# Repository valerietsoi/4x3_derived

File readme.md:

# 4x3 derived

## description 
4x3, four columns and three rows.

Derived, as in derived from the [previous 2x2 macropad](https://github.com/valerietsoi/2squared).

PCB and firmware tested.

Stabless only.

<br>

## pics
| | |
| --- | --- |
|  | |
|  |  |
|  |  |
<br>

## firmware

Use [QMK toolbox](https://qmk.fm/toolbox) to flash the pre-compiled `.bin`. Source files to be uploaded.

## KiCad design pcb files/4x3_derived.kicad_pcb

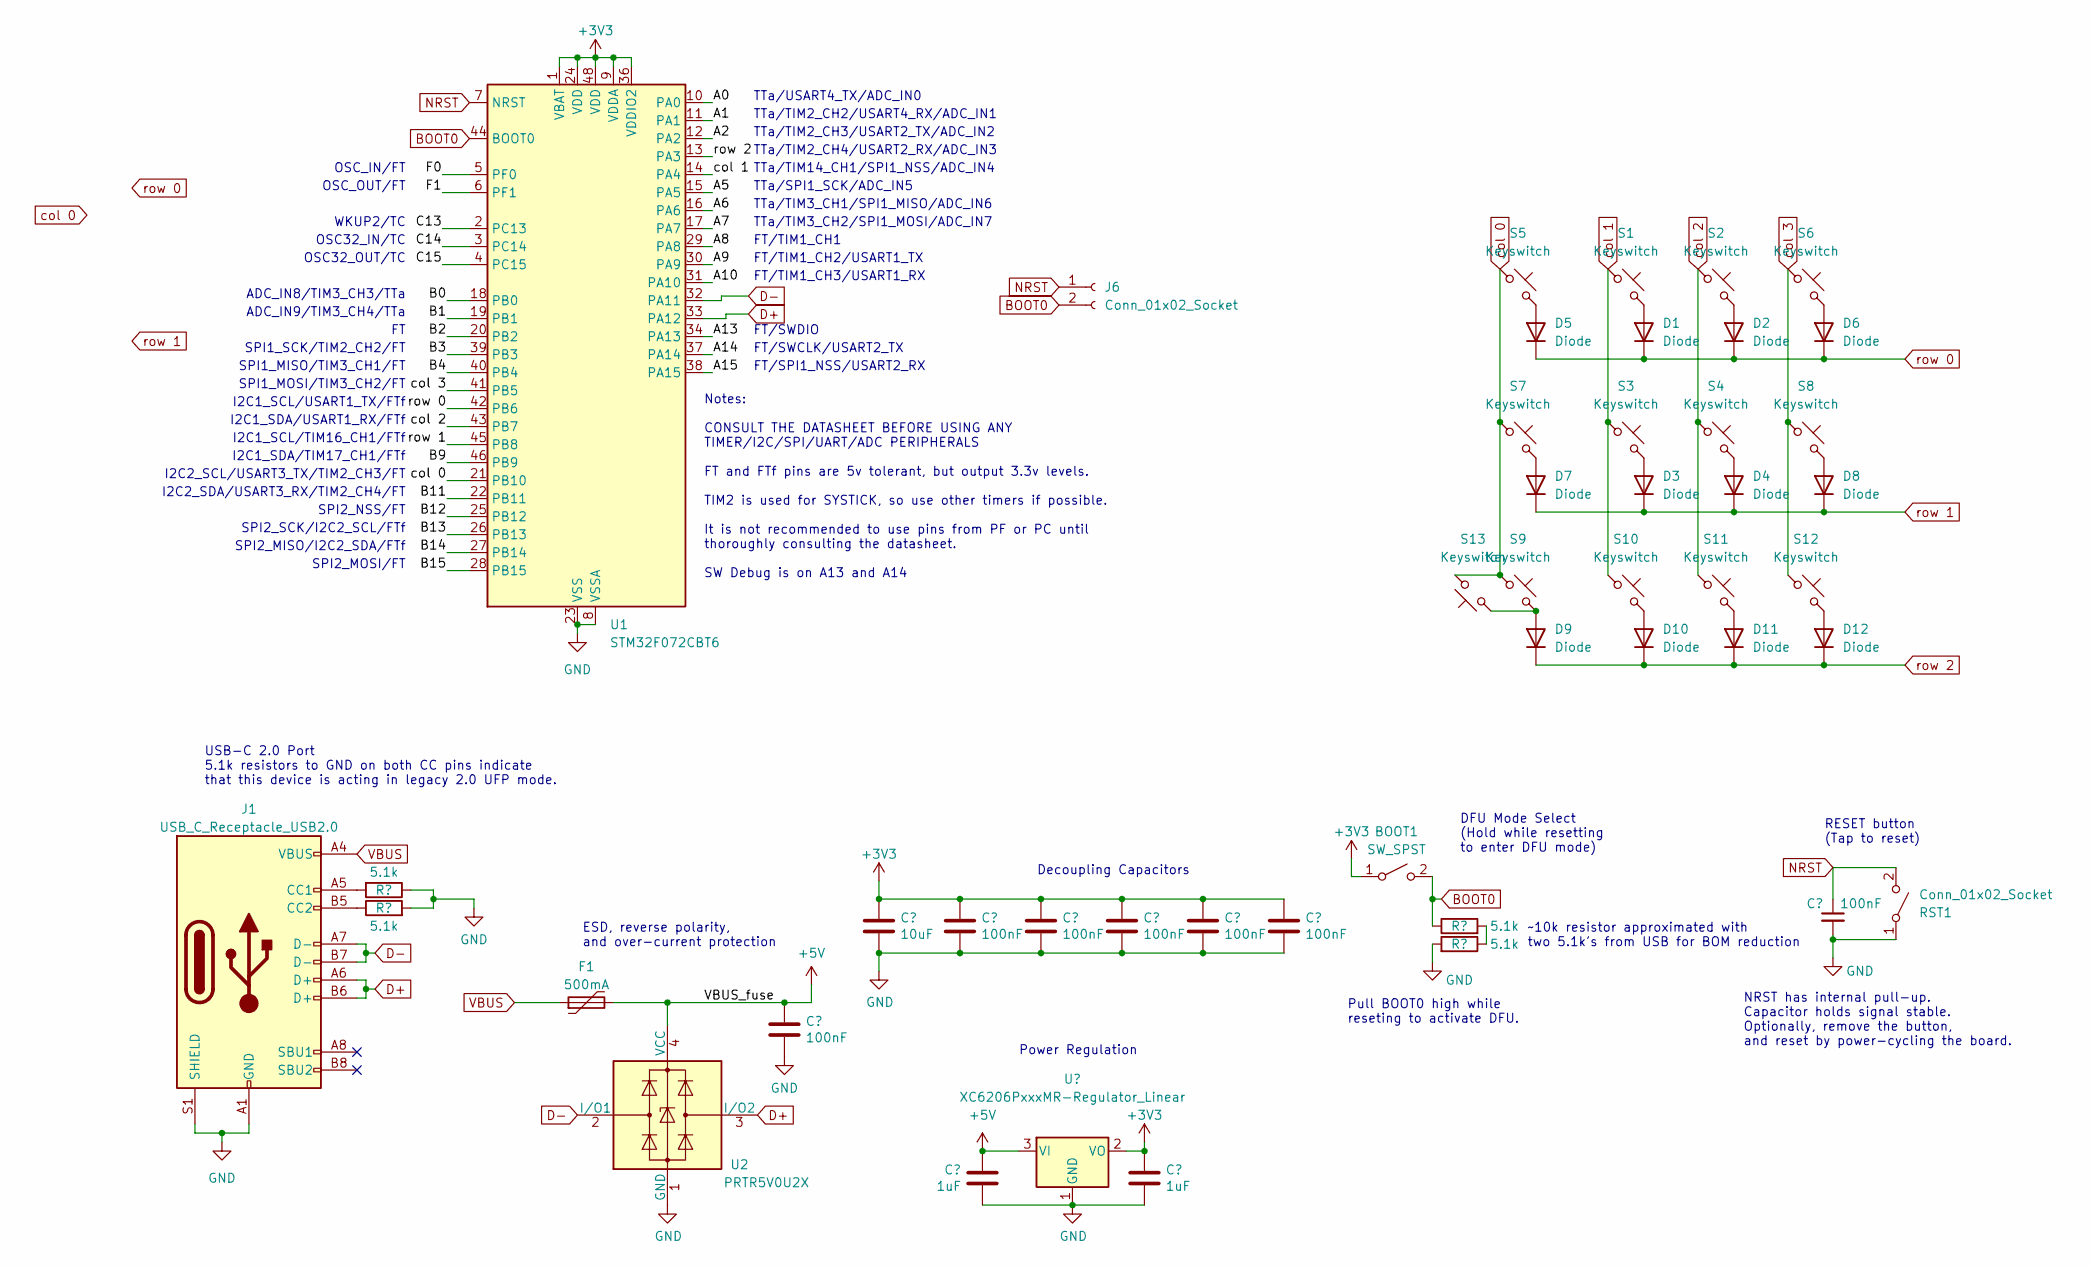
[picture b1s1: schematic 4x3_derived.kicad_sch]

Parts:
BOOT1: SW_SPST; SW_SPST_TL3342
C1, C3, C4, C5, C6, C7, C8: 100nF; C_0402_1005Metric; LCSC C307331
C2: 10uF; C_0603_1608Metric; LCSC C307331
C9, C10: 1uF; C_0402_1005Metric; LCSC C307331
D1, D2, D3, D4, D5, D6, D7, D8, D9, D10, D11, D12: Diode; Diode_SOD-123
F1: 500mA; Fuse_1206_3216Metric; LCSC C135341
J1: USB_C_Receptacle_USB2.0; USB_C_Receptacle_HRO_TYPE-C-31-M-12; JlcRotOffset 180
J6: Conn_01x02_Socket; PinHeader_1x02_P2.54mm_Vertical
R1, R2, R3, R4: 5.1k; R_0402_1005Metric
RST1: Conn_01x02_Socket; PinHeader_1x02_P2.54mm_Vertical
S1, S2, S3, S4, S5, S6, S7, S8, S9, S10, S11, S12, S13: Keyswitch; Hotswap_MX_Plated_1.00u
U1: STM32F072CBT6; LQFP-48_7x7mm_P0.5mm; JlcRotOffset 90
U2: PRTR5V0U2X; SOT-143; LCSC C2827688
U3: XC6206PxxxMR-Regulator_Linear; SOT-23; LCSC C5446

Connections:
/A0: U1.10 (PA0)
/A1: U1.11 (PA1)
/A2: U1.12 (PA2)
/A5: U1.15 (PA5)
/A6: U1.16 (PA6)
/A7: U1.17 (PA7)
/A8: U1.29 (PA8)
/A9: U1.30 (PA9)
/A10: U1.31 (PA10)
/A13: U1.34 (PA13)
/A14: U1.37 (PA14)
/A15: U1.38 (PA15)
/B0: U1.18 (PB0)
/B1: U1.19 (PB1)
/B2: U1.20 (PB2)
/B3: U1.39 (PB3)
/B4: U1.40 (PB4)
/B9: U1.46 (PB9)
/B11: U1.22 (PB11)
/B12: U1.25 (PB12)
/B13: U1.26 (PB13)
/B14: U1.27 (PB14)
/B15: U1.28 (PB15)
/C13: U1.2 (PC13)
/C14: U1.3 (PC14)
/C15: U1.4 (PC15)
/F0: U1.5 (PF0)
/F1: U1.6 (PF1)
BOOT0: BOOT1.2 (B), J6.2, R3.1, U1.44 (BOOT0)
D+: J1.A6 (D+), J1.B6 (D+), U1.33 (PA12), U2.3 (I/O2)
D-: J1.A7 (D-), J1.B7 (D-), U1.32 (PA11), U2.2 (I/O1)
GND: C1.2, C2.2, C3.2, C4.2, C5.2, C6.2, C7.2, C8.2, C9.2, C10.2, J1.A1 (GND), J1.A12 (GND), J1.B1 (GND), J1.B12 (GND), J1.S1 (SHIELD), R1.1, R2.2, R4.2, U1.8 (VSSA), U1.23 (VSS), U1.35 (VSS), U1.47 (VSS), U2.1 (GND), U3.1 (GND); also elsewhere on the board
unnamed: D1.2 (A), S1.2
unnamed: D2.2 (A), S2.2
unnamed: D3.2 (A), S3.2
unnamed: D4.2 (A), S4.2
unnamed: D5.2 (A), S5.2
unnamed: D6.2 (A), S6.2
unnamed: D7.2 (A), S7.2
unnamed: D8.2 (A), S8.2
unnamed: D9.2 (A), S9.2, S13.1
unnamed: D10.2 (A), S10.2
unnamed: D11.2 (A), S11.2
unnamed: D12.2 (A), S12.2
unnamed: J1.A5 (CC1), R1.2
unnamed: J1.B5 (CC2), R2.1
unnamed: R3.2, R4.1
VBUS: F1.1, J1.A4 (VBUS), J1.A9 (VBUS), J1.B4 (VBUS), J1.B9 (VBUS)
col 0: S5.1, S7.1, S9.1, S13.2, U1.21 (PB10)
col 1: S1.1, S3.1, S10.1, U1.14 (PA4)
col 2: S2.1, S4.1, S11.1, U1.43 (PB7)
col 3: S6.1, S8.1, S12.1, U1.41 (PB5)
row 0: D1.1 (K), D2.1 (K), D5.1 (K), D6.1 (K), U1.42 (PB6)
row 1: D3.1 (K), D4.1 (K), D7.1 (K), D8.1 (K), U1.45 (PB8)
row 2: D9.1 (K), D10.1 (K), D11.1 (K), D12.1 (K), U1.13 (PA3)

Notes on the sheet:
RESET button (Tap to reset)
FT/TIM1_CH2/USART1_TX
Decoupling Capacitors
SPI2_SCK/I2C2_SCL/FTf
OSC_IN/FT
TTa/TIM2_CH2/USART4_RX/ADC_IN1
I2C2_SCL/USART3_TX/TIM2_CH3/FT
DFU Mode Select (Hold while resetting to enter DFU mode)
TTa/SPI1_SCK/ADC_IN5
SPI1_MOSI/TIM3_CH2/FT
TTa/USART4_TX/ADC_IN0
SPI2_NSS/FT
I2C1_SCL/TIM16_CH1/FTf
I2C1_SCL/USART1_TX/FTf
TTa/TIM14_CH1/SPI1_NSS/ADC_IN4
SPI1_MISO/TIM3_CH1/FT
ADC_IN9/TIM3_CH4/TTa
TTa/TIM3_CH1/SPI1_MISO/ADC_IN6
USB-C 2.0 Port 5.1k resistors to GND on both CC pins indicate that this device is acting in legacy 2.0 UFP mode.
I2C2_SDA/USART3_RX/TIM2_CH4/FT
SPI2_MISO/I2C2_SDA/FTf
TTa/TIM2_CH3/USART2_TX/ADC_IN2
Power Regulation
OSC_OUT/FT
ESD, reverse polarity, and over-current protection
I2C1_SDA/TIM17_CH1/FTf
OSC32_OUT/TC
FT/SWCLK/USART2_TX
OSC32_IN/TC
FT/SPI1_NSS/USART2_RX
TTa/TIM2_CH4/USART2_RX/ADC_IN3
FT/TIM1_CH3/USART1_RX
NRST has internal pull-up. Capacitor holds signal stable. Optionally, remove the button, and reset by power-cycling the board.
~10k resistor approximated with two 5.1k's from USB for BOM reduction
I2C1_SDA/USART1_RX/FTf
FT/TIM1_CH1
Notes: CONSULT THE DATASHEET BEFORE USING ANY TIMER/I2C/SPI/UART/ADC PERIPHERALS FT and FTf pins are 5v tolerant, but output 3.3v levels. TIM2 is used for SYSTICK, so use other timers if possible. It is not recommended to use pins from PF or PC until thoroughly consulting the datasheet. SW Debug is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
WKUP2/TC
Pull BOOT0 high while reseting to activate DFU.
TTa/TIM3_CH2/SPI1_MOSI/ADC_IN7

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
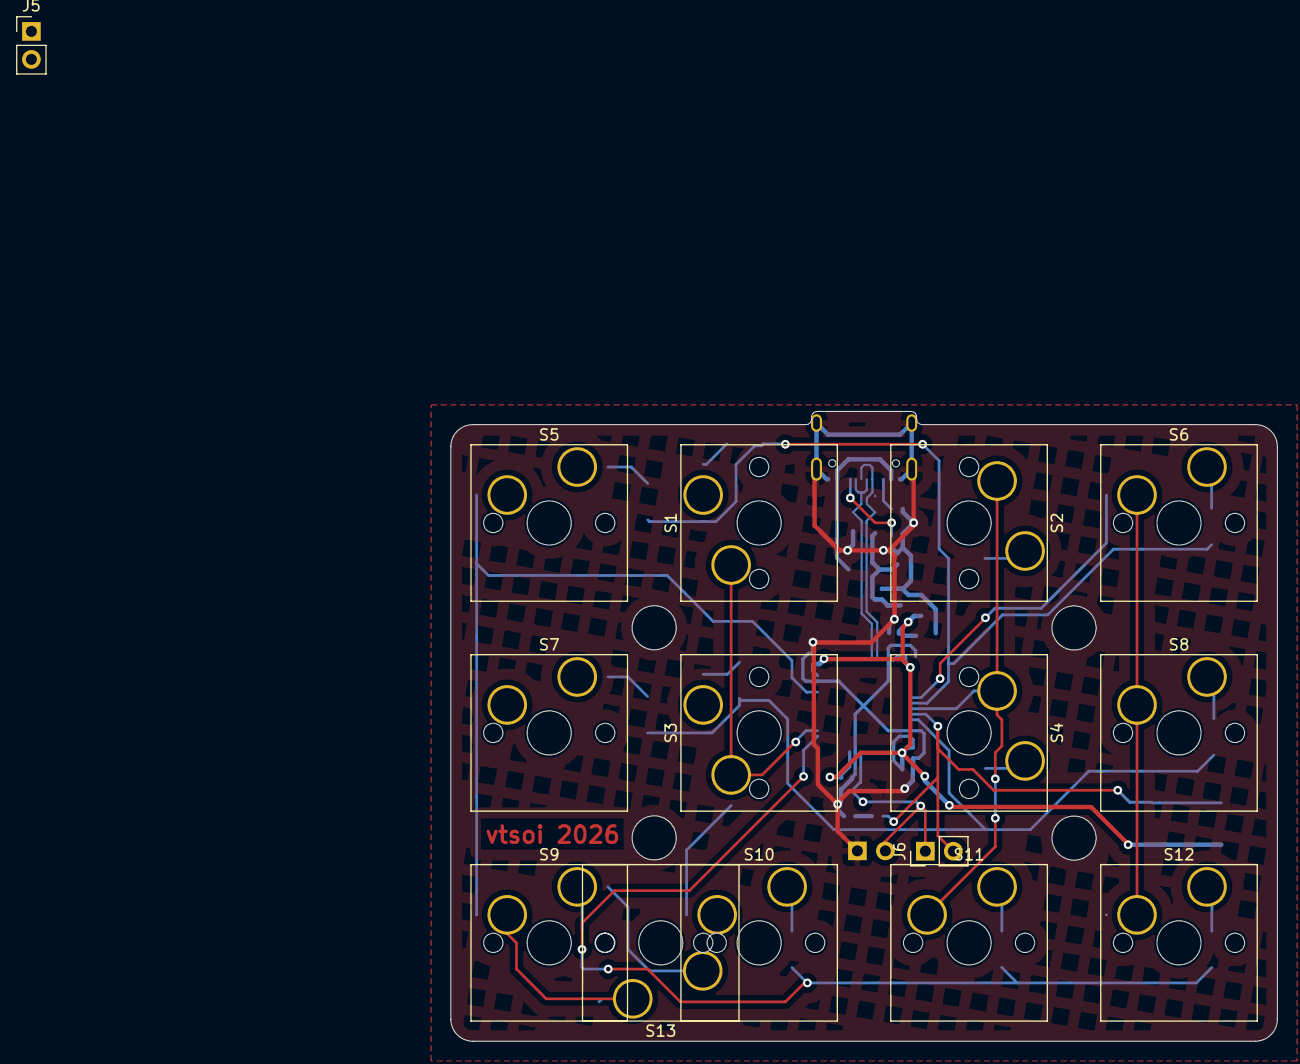
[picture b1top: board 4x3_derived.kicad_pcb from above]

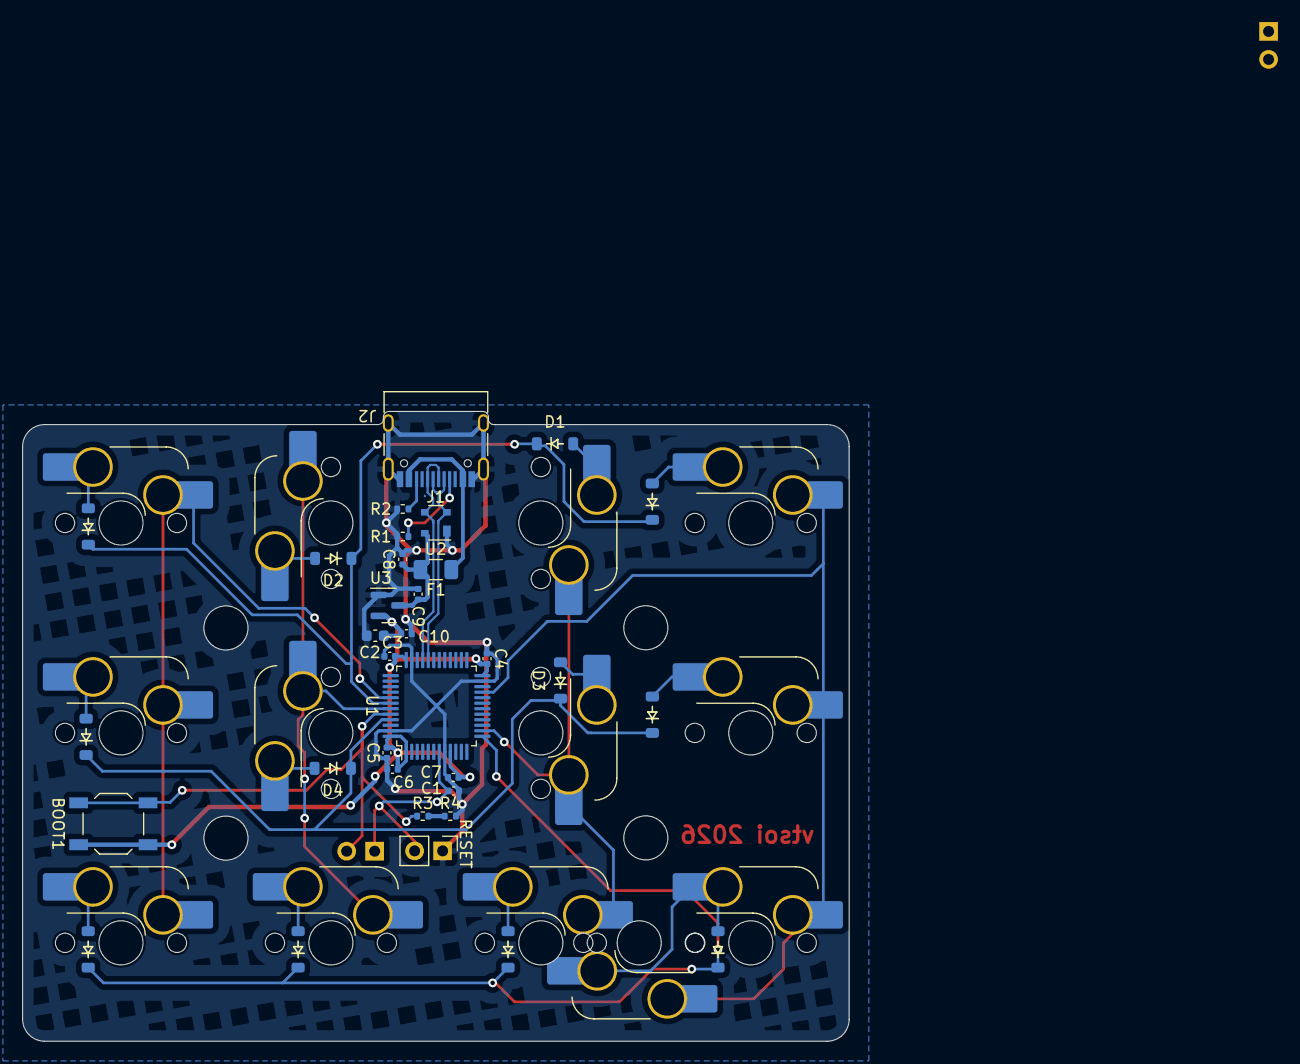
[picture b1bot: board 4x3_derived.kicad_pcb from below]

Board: 2 copper layers, 75.0 x 57.2 mm, 48 parts (33 on the bottom side), 30 nets.

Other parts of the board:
J5: Conn_01x02_Socket; PinHeader_1x02_P2.54mm_Vertical
RESET: Conn_01x02_Socket; PinHeader_1x02_P2.54mm_Vertical

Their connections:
GND: J5.1 (A), RESET.1 (A); also elsewhere on the board

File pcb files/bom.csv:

Designator,Footprint,Quantity,Value,LCSC Part #
BOOT1,SW_SPST_TL3342,1,SW_SPST,C318884
"C1, C10, C3, C5, C6, C8, C9",0402,7,100nF,C1525
C2,0603,1,10uF,C19702
"C4, C7",0402,2,1uF,C52923
"D1, D10, D11, D12, D2, D3, D4, D5, D6, D7, D8, D9",Diode_SOD-123,12,Diode,C81598
F1,1206,1,500mA,C369160
J1,USB_C_Receptacle_HRO_TYPE-C-31-M-12,1,USB_C_Receptacle_USB2.0,
"J6, RESET",PinHeader_1x02_P2.54mm_Vertical,2,Conn_01x02_Socket,
"R1, R2, R3, R4",0402,4,5.1k,C25905
"S1, S10, S11, S12, S2, S3, S4, S5, S6, S7, S8, S9",Hotswap_MX_Plated_1.00u,12,Keyswitch,
U1,LQFP-48_7x7mm_P0.5mm,1,STM32F072CBT6,C81720
U2,SOT-143,1,PRTR5V0U2X,C2827688
U3,SOT-23,1,XC6206PxxxMR-Regulator_Linear,C5446

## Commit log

2026-02-17 files added
2026-02-17 reorganised
2026-02-17 readme, pics, and firmware
2026-02-17 minor
2026-02-17 renders added
2026-02-19 case files
2026-03-10 pcb updated
2026-03-31 2u compatible integrated plate top case
2026-03-31 updated firmware
2026-04-02 multilayout firmware and updated images
2026-04-02 readme
2026-04-02 source
